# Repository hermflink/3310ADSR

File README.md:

# 3310ADSR
Dual ADSR based on AS3310

Kicad project files of a dual ADSR based on two AS3310 components. Part of a modular DIY synth project, other modules are available in other repositories. Likely compatible with a CEM3310.

Used the Audio.lib from https://kicad.github.io/symbols/Audio to extend the Kicad library for the AS3310 component.

Designed to work with +/- 15V, not tested for +/- 12V

The PCB is 9.5 x 5.5 cm and has no PCB-mounting of potmeters, switches, jacks; these are all connected by pin header connectors

Important note: Gate must never be unconnected, so must be either GND (off) or 2.6 to 15V (on), otherwise release will never occur. Applying a negative voltage to the gate will break your AS3310!!!

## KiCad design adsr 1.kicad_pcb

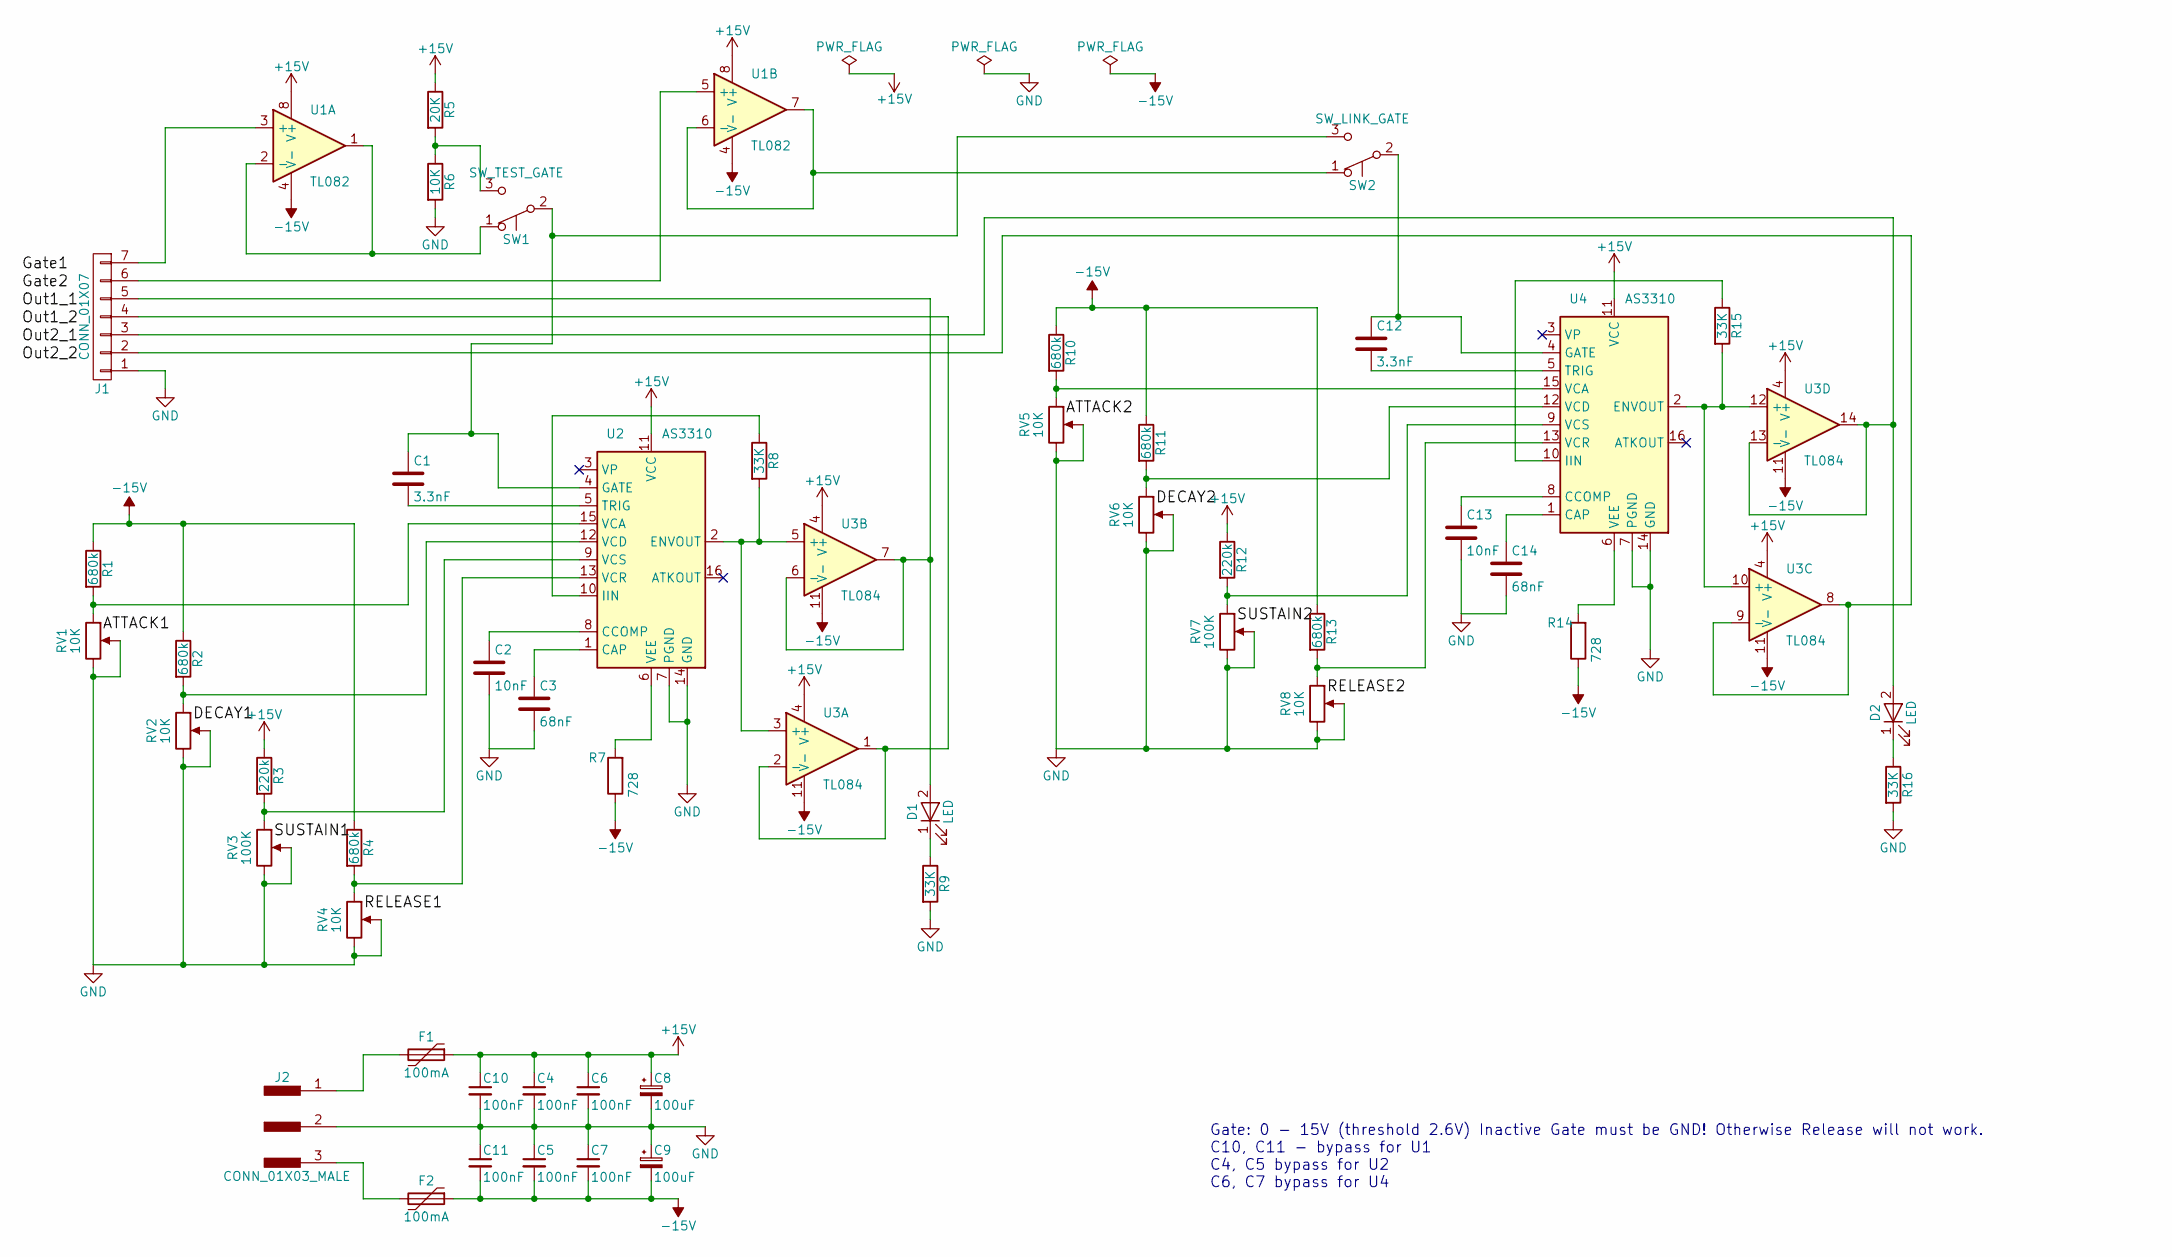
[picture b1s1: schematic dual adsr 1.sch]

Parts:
C1, C12: 3.3nF; C_Disc_D4.3mm_W1.9mm_P5.00mm
C2, C13: 10nF; C_Disc_D4.3mm_W1.9mm_P5.00mm
C3, C14: 68nF; C_Disc_D4.3mm_W1.9mm_P5.00mm
C4, C5, C6, C7, C10, C11: 100nF; C_Disc_D5.0mm_W2.5mm_P5.00mm
C8, C9: 100uF; CP_Radial_D8.0mm_P2.50mm
D1, D2: LED; Pin_Header_Straight_1x02_Pitch2.54mm
F1, F2: 100mA; C_Disc_D6.0mm_W2.5mm_P5.00mm
J1: CONN_01X07; Pin_Header_Straight_1x07_Pitch2.54mm
J2: CONN_01X03_MALE; Pin_Header_Straight_1x03_Pitch2.54mm
R1, R2, R4, R10, R11, R13: 680k; R_Axial_DIN0207_L6.3mm_D2.5mm_P2.54mm_Vertical
R3, R12: 220k; R_Axial_DIN0207_L6.3mm_D2.5mm_P2.54mm_Vertical
R5: 20K; R_Axial_DIN0207_L6.3mm_D2.5mm_P2.54mm_Vertical
R6: 10K; R_Axial_DIN0207_L6.3mm_D2.5mm_P2.54mm_Vertical
R7, R14: 728; R_Axial_DIN0207_L6.3mm_D2.5mm_P2.54mm_Vertical
R8, R9, R15, R16: 33K; R_Axial_DIN0207_L6.3mm_D2.5mm_P2.54mm_Vertical
RV1, RV2, RV4, RV5, RV6, RV8: 10K; Pin_Header_Straight_1x03_Pitch2.54mm
RV3, RV7: 100K; Pin_Header_Straight_1x03_Pitch2.54mm
SW1: SW_TEST_GATE; Pin_Header_Straight_1x03_Pitch2.54mm
SW2: SW_LINK_GATE; Pin_Header_Straight_1x03_Pitch2.54mm
U1: TL082; DIP-8_W7.62mm
U2, U4: AS3310; DIP-16_W7.62mm
U3: TL084; DIP-14_W7.62mm

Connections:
+15V: C4.1, C6.1, C8.1, C10.1, F1.1, R3.1, R5.1, R12.1, U1.8 (V+), U2.11 (VCC), U3.4 (V+), U4.11 (VCC)
-15V: C5.2, C7.2, C9.2, C11.2, F2.1, R1.1, R2.1, R4.1, R7.1, R10.1, R11.1, R13.1, R14.1, U1.4 (V-), U3.11 (V-)
GND: C2.2, C3.2, C4.2, C5.1, C6.2, C7.1, C8.2, C9.1, C10.2, C11.1, C13.2, C14.2, J1.1, J2.2, R6.2, R9.2, R16.2, RV1.2, RV1.3, RV2.2, RV2.3, RV3.2, RV3.3, RV4.2, RV4.3, RV5.2, RV5.3, RV6.2, RV6.3, RV7.2, RV7.3, RV8.2, RV8.3, U2.7 (PGND), U2.14 (GND), U4.7 (PGND), U4.14 (GND)
unnamed: C1.1, SW1.2 (B), SW2.3 (C), U2.4 (GATE)
unnamed: C1.2, U2.5 (TRIG)
unnamed: C2.1, U2.8 (CCOMP)
unnamed: C3.1, U2.1 (CAP)
unnamed: C12.1, SW2.2 (B), U4.4 (GATE)
unnamed: C12.2, U4.5 (TRIG)
unnamed: C13.1, U4.8 (CCOMP)
unnamed: C14.1, U4.1 (CAP)
unnamed: D1.1 (K), R9.1
unnamed: D1.2 (A), J1.5, U3.6 (-), U3.7
unnamed: D2.1 (K), R16.1
unnamed: D2.2 (A), J1.3, U3.13 (-), U3.14
unnamed: F1.2, J2.1
unnamed: F2.2, J2.3
unnamed: J1.2, U3.8, U3.9 (-)
unnamed: J1.4, U3.1, U3.2 (-)
unnamed: J1.6, U1.5 (+)
unnamed: J1.7, U1.3 (+)
unnamed: R1.2, RV1.1, U2.15 (VCA)
unnamed: R2.2, RV2.1, U2.12 (VCD)
unnamed: R3.2, RV3.1, U2.9 (VCS)
unnamed: R4.2, RV4.1, U2.13 (VCR)
unnamed: R5.2, R6.1, SW1.3 (C)
unnamed: R7.2, U2.6 (VEE)
unnamed: R8.1, U2.10 (IIN)
unnamed: R8.2, U2.2 (ENVOUT), U3.3 (+), U3.5 (+)
unnamed: R10.2, RV5.1, U4.15 (VCA)
unnamed: R11.2, RV6.1, U4.12 (VCD)
unnamed: R12.2, RV7.1, U4.9 (VCS)
unnamed: R13.2, RV8.1, U4.13 (VCR)
unnamed: R14.2, U4.6 (VEE)
unnamed: R15.1, U4.10 (IIN)
unnamed: R15.2, U3.10 (+), U3.12 (+), U4.2 (ENVOUT)
unnamed: SW1.1 (A), U1.1, U1.2 (-)
unnamed: SW2.1 (A), U1.6 (-), U1.7

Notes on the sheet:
Gate: 0 - 15V (threshold 2.6V) Inactive Gate must be GND! Otherwise Release will not work. C10, C11 - bypass for U1 C4, C5 bypass for U2 C6, C7 bypass for U4

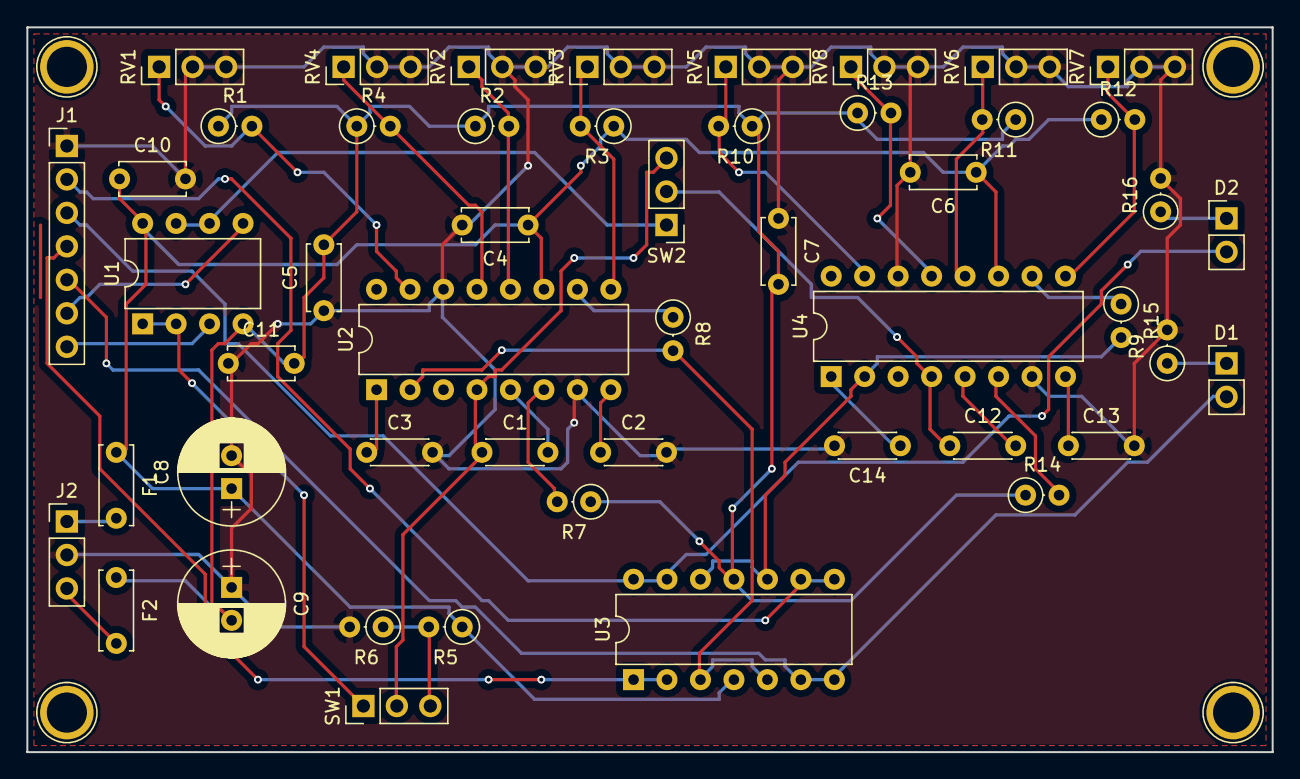
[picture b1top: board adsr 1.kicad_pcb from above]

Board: 2 copper layers, 94.5 x 55.0 mm, 50 parts (0 on the bottom side), 38 nets.

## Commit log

2019-11-08 Create LICENSE
